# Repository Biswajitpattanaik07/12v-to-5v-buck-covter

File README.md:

<div align="center">

# 12V to 5V Buck Converter

**A compact, high-efficiency step-down DC-DC converter built on the LM2596-5.0, with a complete 2-layer KiCad PCB design.**

[Overview](#overview) •
[Features](#features) •
[Specifications](#specifications) •
[How It Works](#how-it-works) •
[Schematic](#schematic) •
[PCB](#pcb-design) •
[Getting Started](#getting-started) •
[Testing](#testing) •
[Results](#results) •
[Roadmap](#roadmap)

</div>

---

## Table of Contents

- [Overview](#overview)
- [Features](#features)
- [Specifications](#specifications)
- [How It Works](#how-it-works)
- [Design Calculations](#design-calculations)
- [Schematic](#schematic)
- [Bill of Materials](#bill-of-materials)
- [PCB Design](#pcb-design)
- [Repository Structure](#repository-structure)
- [Getting Started](#getting-started)
- [Assembly Guide](#assembly-guide)
- [Testing](#testing)
- [Results](#results)
- [Troubleshooting](#troubleshooting)
- [Applications](#applications)
- [Limitations](#limitations)
- [Roadmap](#roadmap)
- [Contributing](#contributing)
- [License](#license)
- [References](#references)
- [Author](#author)

---

## Overview

Most digital electronics run on 5 V, but common power sources such as batteries, adapters, and car supplies provide 12 V. A linear regulator like the 7805 can do the conversion, but it turns the extra 7 V into heat: at 2 A that is about 14 W wasted, and the efficiency is only around 42%.

This project replaces that approach with a **buck (step-down) switching converter**. The LM2596 chops the 12 V input at 150 kHz, and an inductor and capacitor smooth it into a clean 5 V output. The result is roughly **twice the efficiency**, about **one-sixth of the heat**, and no heat sink.

The repository contains the schematic, PCB layout, design calculations, bill of materials, test procedure, and a full project report.

> **Why this project?** It is a practical, buildable example of power-supply design: component selection, derating, thermal design, and the PCB layout practice that decides whether a switching supply works well or badly.

---

## Features

- Input range of **9 V to 15 V** (the IC itself accepts up to 40 V)
- Fixed **5 V output** at up to **3 A** (2 A continuous design point)
- **About 81% efficiency** at 2 A, compared with about 42% for a 7805
- **150 kHz** fixed switching frequency, which keeps the inductor and capacitors small
- Output ripple targeted below **50 mV peak-to-peak**
- Built-in **thermal shutdown** and **current limiting**
- Compact **50 mm x 35 mm** 2-layer board with a solid ground plane
- Power indicator LED
- Open hardware: all design files, calculations, and documentation included

---

## Specifications

| Parameter | Value |
|---|---|
| Input voltage | 12 V nominal (9 V to 15 V) |
| Output voltage | 5 V fixed |
| Output current | 2 A continuous, 3 A maximum |
| Switching frequency | 150 kHz |
| Regulator IC | LM2596S-5.0 (TO-263) |
| Topology | Asynchronous buck (Schottky freewheeling diode) |
| Inductor ripple | about 30% of load current (0.6 A) |
| Output ripple | below 50 mV peak-to-peak (target) |
| Efficiency | about 81% at 2 A, 12 V input (estimated) |
| PCB | 2-layer FR4, 1.6 mm, 1 oz copper, 50 x 35 mm |

---

## How It Works

The converter is built from a switch, an inductor, a diode, and an output capacitor.

Each 6.67 microsecond switching cycle has two phases:

| Phase | What happens |
|---|---|
| **Switch ON** | The input feeds the inductor. Its current ramps up and it stores energy. The diode is off. |
| **Switch OFF** | The inductor keeps pushing current through the Schottky diode to the load while its current ramps down. |

The output voltage is set by the duty cycle `D` (the fraction of each cycle the switch is on):

```
Vout = D x Vin        =>    D = 5 V / 12 V = 0.417
```

The LM2596 monitors the output through its feedback pin and adjusts `D` automatically, so the output stays at 5 V when the input or the load changes.

---

## Design Calculations

| Item | Formula | Result |
|---|---|---|
| Duty cycle | `D = Vout / Vin` | 0.417 (about 0.476 with diode and switch drops) |
| Inductor ripple | `dIL = 0.3 x Iout` | 0.6 A |
| Inductor | `L = (Vin - Vout) x D / (fsw x dIL)` | 32.4 uH, so **33 uH** (Isat of at least 4 A) |
| Output capacitor | ESR-limited ripple, `dIL x ESR` | **220 uF / 16 V low-ESR** + 10 uF ceramic |
| Input capacitor | `Icin(rms) = Iout x sqrt(D(1-D))` | about 1 A, so **470 uF / 25 V low-ESR** + 10 uF ceramic |
| Schottky diode | `Id(avg) = Iout x (1-D)` | 1.17 A average, so **3 A / 40 V** (SS34 or 1N5822) |
| Estimated loss | switch + switching + diode + inductor + ESR + quiescent | about 2.3 W |
| Efficiency | `Pout / (Pout + Ploss)` | about 81% |
| Junction temperature | `Ta + P(IC) x thetaJA` | about 70 C at 25 C ambient |

The full derivations are in [`docs/Project_Report.docx`](docs/Project_Report.docx).

---

## Schematic

**Connections**

- `J1` brings in 12 V, filtered by the 470 uF electrolytic and 10 uF ceramic input capacitors.
- `U1` (LM2596-5.0) pin 1 is VIN and pin 3 is GND. Pin 5 (ON/OFF) is grounded to keep the regulator always enabled.
- Pin 2 is the switch node, connected to the Schottky diode cathode and to inductor `L1`.
- The output of `L1` is the 5 V rail, filtered by the 220 uF and 10 uF capacitors and fed back to pin 4.
- A red LED with a 1 k resistor indicates that 5 V is present.

---

## Bill of Materials

| Ref | Component | Value / Part No. | Qty | Package |
|---|---|---|---|---|
| U1 | Buck regulator | LM2596S-5.0 | 1 | TO-263-5 |
| L1 | Power inductor | 33 uH, Isat of at least 4 A | 1 | Shielded SMD or radial |
| D1 | Schottky diode | SS34 or 1N5822 | 1 | SMC or DO-201 |
| C1 | Electrolytic capacitor | 470 uF, 25 V, low ESR | 1 | Radial 8 mm |
| C2 | Ceramic capacitor | 10 uF, 25 V, X7R | 1 | 1206 |
| C3 | Electrolytic capacitor | 220 uF, 16 V, low ESR | 1 | Radial 6.3 mm |
| C4 | Ceramic capacitor | 10 uF, 16 V, X7R | 1 | 1206 |
| R1 | Resistor | 1 k, 1% | 1 | 0805 |
| LED1 | Indicator LED | Red | 1 | 3 mm or 0805 |
| J1, J2 | Screw terminal | 2-pin, 5.08 mm pitch | 2 | Through-hole |
| PCB | FR4, 2-layer | 50 x 35 mm, 1.6 mm | 1 | - |

> **Component tips**
> - Use **low-ESR** electrolytics rated for 105 C. Ordinary ones cause high ripple and heating.
> - Pick the inductor by **saturation current**, not just its RMS rating.
> - Do **not** substitute a 1N4007 for the Schottky diode. It is too slow and drops too much voltage.

---

## PCB Design

| Parameter | Value |
|---|---|
| Layers | 2 (top: components and power, bottom: ground plane) |
| Board size | 50 mm x 35 mm |
| Power trace width | 1.5 mm minimum (2 to 3 mm where possible) |
| Clearance | 0.3 mm minimum (0.5 mm on 12 V nets) |
| Via | 0.8 mm pad / 0.4 mm drill |
| Finish | HASL (lead-free) or ENIG |

**Layout rules followed**

1. **Keep the hot loop small.** The input ceramic capacitor sits within 3 mm of the IC's VIN and GND pins.
2. **Keep the switch node small.** The node between U1, D1, and L1 swings from about -0.5 V to 12 V at 150 kHz and behaves like an antenna.
3. **Use a solid ground plane** on the bottom layer, with stitching vias next to every power-ground pad.
4. **Route feedback away from the inductor** and from the switch node.
5. **Use thermal copper.** The IC tab is soldered to a roughly 6 cm2 pour tied to the ground plane through 6 to 9 thermal vias.
6. **Separate input and output connectors** onto opposite edges of the board.

---

## Repository Structure

```
buck-converter-12v-5v/
├── README.md
├── LICENSE
├── assets/                    # Images used in this README
│   ├── banner.png
│   ├── block_diagram.png
│   ├── operating_modes.png
│   ├── waveforms.png
│   ├── schematic.png
│   ├── pcb_layout.png
│   └── efficiency_curve.png
├── docs/
│   └── Project_Report.docx    # Full project report
├── hardware/                  # (add your files here)
│   ├── kicad/                 # .kicad_pro, .kicad_sch, .kicad_pcb
│   ├── gerbers/               # Fabrication files (zip for upload)
│   └── bom/                   # BOM and pick-and-place files
└── test-data/                 # (add your files here) measurements, scope captures
```

---

## Getting Started

### Prerequisites

- [KiCad 8](https://www.kicad.org/download/) (or newer) to open or edit the design
- A soldering iron or hot-air station, and a multimeter
- A bench power supply (12 V, 3 A or more)
- An oscilloscope, if you want to check ripple

### Clone the repository

```bash
git clone https://github.com/<your-username>/buck-converter-12v-5v.git
cd buck-converter-12v-5v
```

### Open the design

1. Launch KiCad and open `hardware/kicad/buck_converter.kicad_pro`.
2. Open the schematic editor and run **Inspect > Electrical Rules Checker**.
3. Open the PCB editor and run **Inspect > Design Rules Checker**. It should report 0 errors.

### Order the PCB

1. In the PCB editor choose **File > Fabrication Outputs > Gerbers** and **Drill Files**.
2. Zip the outputs, or use the zip already in `hardware/gerbers/`.
3. Upload the zip to a fabricator such as JLCPCB, PCBWay, or OSH Park.
4. Select: 2 layers, 1.6 mm FR4, 1 oz copper, HASL lead-free.

---

## Assembly Guide

1. Place and solder the **small SMD parts** first: ceramic capacitors, resistor, LED, and diode.
2. Solder the **LM2596 (TO-263)**. Make sure the metal tab makes a solid joint with the copper pad, since this is the main heat path.
3. Solder the **inductor**, then the **electrolytic capacitors** (check polarity).
4. Fit the **screw terminals** last.
5. Clean flux with isopropyl alcohol and inspect for solder bridges.

> **Before powering on:** with a multimeter in continuity mode, confirm there is **no short** between VIN and GND, or between 5 V and GND.

---

## Testing

| Step | Test | Expected |
|---|---|---|
| 1 | No-load: apply 12 V with a 0.5 A current limit | Vout about 5 V, input current 5 to 10 mA |
| 2 | Load regulation: 0.5 A to 3 A in steps | Vout stays within about 5 V +/- 0.1 V |
| 3 | Line regulation: vary Vin 9 V to 15 V at 1 A | Vout changes by less than 2% |
| 4 | Ripple: AC-coupled scope, 20 MHz limit, spring ground | below 50 mV peak-to-peak |
| 5 | Thermal: 2 A for 30 minutes | IC tab about 60 to 70 C |
| 6 | Short-circuit: brief short on the output | Current limit trips, normal recovery |

**Formulas**

```
Efficiency (%)      = (Vout x Iout) / (Vin x Iin) x 100
Load regulation (%) = (Vout_noload - Vout_fullload) / Vout_fullload x 100
Line regulation (%) = (Vout_maxVin - Vout_minVin) / Vout_nominal x 100
```

> **Scope tip:** use the probe's spring ground (not the long clip lead) to avoid picking up false noise.

---

## Results

The expected values below come from the design calculations and datasheet characteristics. Replace the **Measured** column with your own bench readings.

| Iout (A) | Expected Vout (V) | Expected efficiency (%) | Measured Vout (V) | Measured efficiency (%) |
|---|---|---|---|---|
| 0.5 | 5.00 | 80 | | |
| 1.0 | 5.00 | 84 | | |
| 1.5 | 4.99 | 83 | | |
| 2.0 | 4.99 | 81 | | |
| 2.5 | 4.98 | 78 | | |
| 3.0 | 4.97 | 75 | | |

### Comparison with a 7805 linear regulator (12 V in, 2 A out)

| Parameter | LM7805 | This design |
|---|---|---|
| Input power | about 24 W | about 12.3 W |
| Power lost as heat | about 14 W | about 2.3 W |
| Efficiency | about 42% | about 81% |
| Heat sink | Large, required | Copper pour only |

---

## Troubleshooting

| Problem | Likely cause | Fix |
|---|---|---|
| No output voltage | ON/OFF pin not grounded, or a missing or reversed diode | Check pin 5 and diode orientation |
| Output is 12 V | Feedback pin not connected | Connect pin 4 to the 5 V rail |
| High ripple or noise | High-ESR capacitor, or a long scope ground lead | Use low-ESR parts and a spring ground |
| IC overheats | Poor solder joint on the tab, or an overload | Re-solder the tab, add more copper, check the load |
| Buzzing or squealing | Inductor saturating or loose | Use an inductor with higher Isat, secure it |
| Output droops under load | Input supply too weak | Use a supply rated for at least 12 V at 2 A |

---

## Applications

- Powering **Arduino, ESP32, and Raspberry Pi** boards from 12 V batteries
- **Automotive** USB chargers (add transient protection first)
- **LED strip** controllers and lighting
- Industrial control panels with a 12 V rail
- **Solar** and battery-powered sensor nodes
- **Robotics**, where 12 V motors and 5 V logic share one battery

---

## Limitations

- Switching ripple and EMI may disturb sensitive analogue circuits unless extra filtering is added.
- The asynchronous design loses some efficiency in the diode compared with a synchronous converter.
- There is no galvanic isolation, and no reverse-polarity or over-voltage protection on the base design.
- Performance depends strongly on following the PCB layout rules.

---

## Roadmap

- [x] Design calculations and component selection
- [x] Schematic and PCB layout
- [x] Project report
- [ ] Add measured results and scope captures to `test-data/`
- [ ] LTspice simulation files
- [ ] Reverse-polarity, TVS, and fuse protection footprints
- [ ] Synchronous buck version for above 90% efficiency
- [ ] Voltage and current monitoring with an INA219 and a microcontroller
- [ ] Adjustable-output variant
- [ ] EMI pre-compliance measurements

---

## Contributing

Contributions are welcome.

1. Fork the repository.
2. Create a feature branch: `git checkout -b feature/my-improvement`
3. Commit your changes: `git commit -m "Add my improvement"`
4. Push to the branch: `git push origin feature/my-improvement`
5. Open a pull request.

Please open an issue first for large changes, and include screenshots for any PCB or schematic modification.

---

## License

This project is released under the **MIT License**. See the [LICENSE](LICENSE) file for details. You are free to use, modify, and distribute the design, but you build and use it at your own risk. Always verify the design before using it in safety-critical equipment.

---

## References

1. Texas Instruments, *LM2596 SIMPLE SWITCHER 150 kHz 3-A Step-Down Voltage Regulator*, datasheet SNVS124.
2. M. H. Rashid, *Power Electronics: Circuits, Devices and Applications*, 4th ed., Pearson.
3. R. W. Erickson and D. Maksimovic, *Fundamentals of Power Electronics*, 2nd ed., Springer.
4. Texas Instruments, *AN-1229 SIMPLE SWITCHER PCB Layout Guidelines*, SNVA054.
5. IPC-2221B, *Generic Standard on Printed Board Design*.
6. [KiCad documentation](https://docs.kicad.org)

---
## Board Images

<table align="center">
  <tr>
    <td align="center">
      <br>
      <sub><b>Image 1</b></sub>
    </td>
    <td align="center">
      <br>
      <sub><b>Image 2</b></sub>
    </td>
  </tr>
  <tr>
    <td align="center" colspan="2">
      <br>
      <sub><b>Image 3 (full view)</b></sub>
    </td>
  </tr>
  <tr>
    <td align="center">
      <br>
      <sub><b>Image 4</b></sub>
    </td>
    <td align="center">
      <br>
      <sub><b>Image 5</b></sub>
    </td>
  </tr>
  <tr>
    <td align="center" colspan="2">
      <br>
      <sub><b>Image 6</b></sub>
    </td>
  </tr>
  <tr>
    <td align="center" colspan="2">
      <br>
      <sub><b>Image 7</b></sub>
    </td>
  </tr>
</table>

## Author

**Biswajit Pattanaik**
Centurion University and Technology,Bhubaneswar , Department of  Electronics  And Communication Engineering

<div align="center">

If this project helped you, please consider giving it a star.

</div>

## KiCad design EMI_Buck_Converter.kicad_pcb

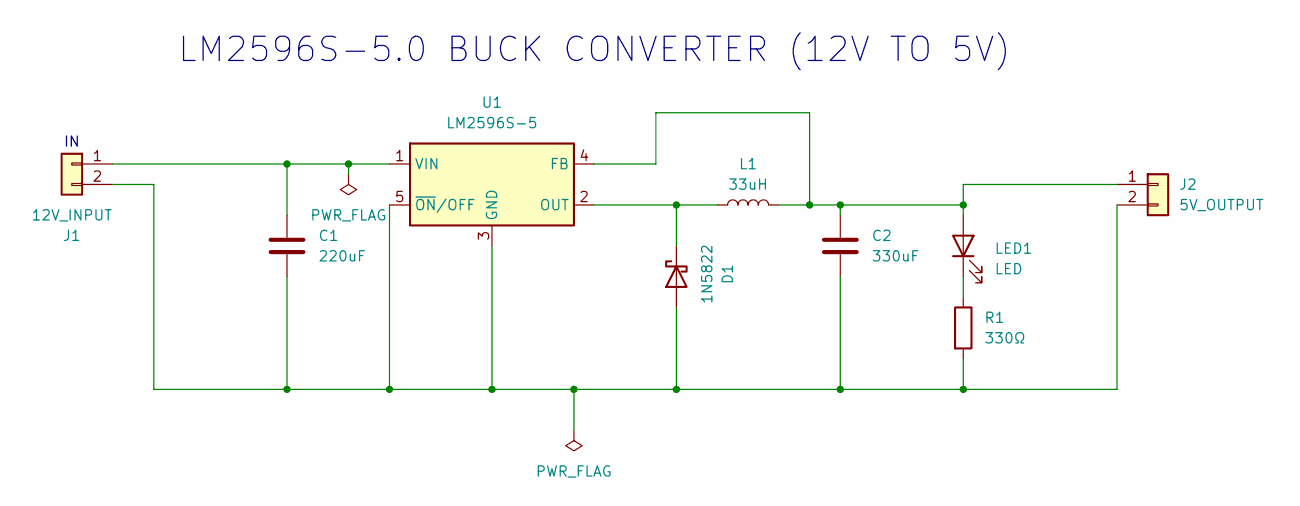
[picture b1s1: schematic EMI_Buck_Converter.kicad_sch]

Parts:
C1: 220uF; CP_Radial_D10.0mm_P5.00mm
C2: 330uF; CP_Radial_D10.0mm_P5.00mm
D1: 1N5822; D_DO-201AD_P15.24mm_Horizontal
J1: 12V_INPUT; TerminalBlock_MaiXu_MX126-5.0-02P_1x02_P5.00mm
J2: 5V_OUTPUT; TerminalBlock_MaiXu_MX126-5.0-02P_1x02_P5.00mm
L1: 33uH; L_Axial_L7.0mm_D3.3mm_P10.16mm_Horizontal_Fastron_MICC
LED1: LED; LED_D3.0mm
R1: 330Ω; R_Axial_DIN0207_L6.3mm_D2.5mm_P7.62mm_Horizontal
U1: LM2596S-5; TO-263-5_TabPin3

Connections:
unnamed: C1.2, C2.2, D1.2 (A), J1.2, J2.2, R1.2, U1.3 (GND), U1.5 (~ON/OFF)
unnamed: D1.1 (K), L1.1, U1.2 (OUT)
unnamed: C1.1, J1.1, U1.1 (VIN)
unnamed: C2.1, J2.1, L1.2, LED1.2 (A), U1.4 (FB)
unnamed: LED1.1 (K), R1.1

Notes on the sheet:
LM2596S-5.0 BUCK CONVERTER (12V TO 5V)

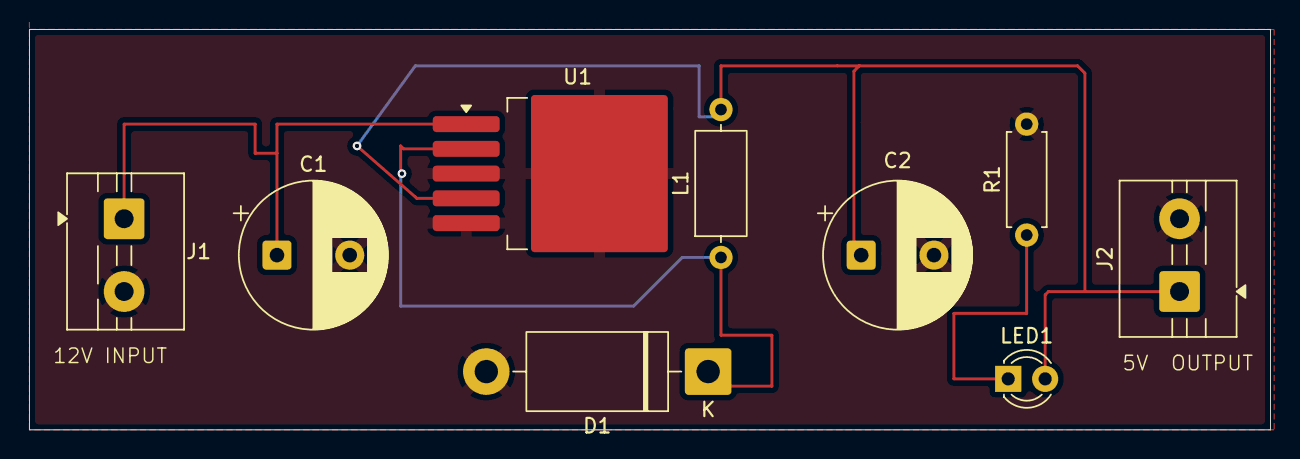
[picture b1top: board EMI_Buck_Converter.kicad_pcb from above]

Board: 2 copper layers, 85.2 x 27.5 mm, 9 parts (0 on the bottom side), 5 nets.

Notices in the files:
README.md:
License: MIT
